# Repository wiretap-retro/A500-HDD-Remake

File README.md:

# A500 HDD Remake
A500 Side Expansion IDE

## Info
The A500 HDD Remake is an Amiga 500 ATA Expansion device that utilitizes ide.device to provide interface for a hard drive or CD-ROM. I use it in my A500 Tower, so I modified it with an activity light header and slightly different dimensions. 
\
\
Design attributed to John Tsiombika's A500hdd device, slightly modified. See additional details at: http://nuclear.mutantstargoat.com/hw

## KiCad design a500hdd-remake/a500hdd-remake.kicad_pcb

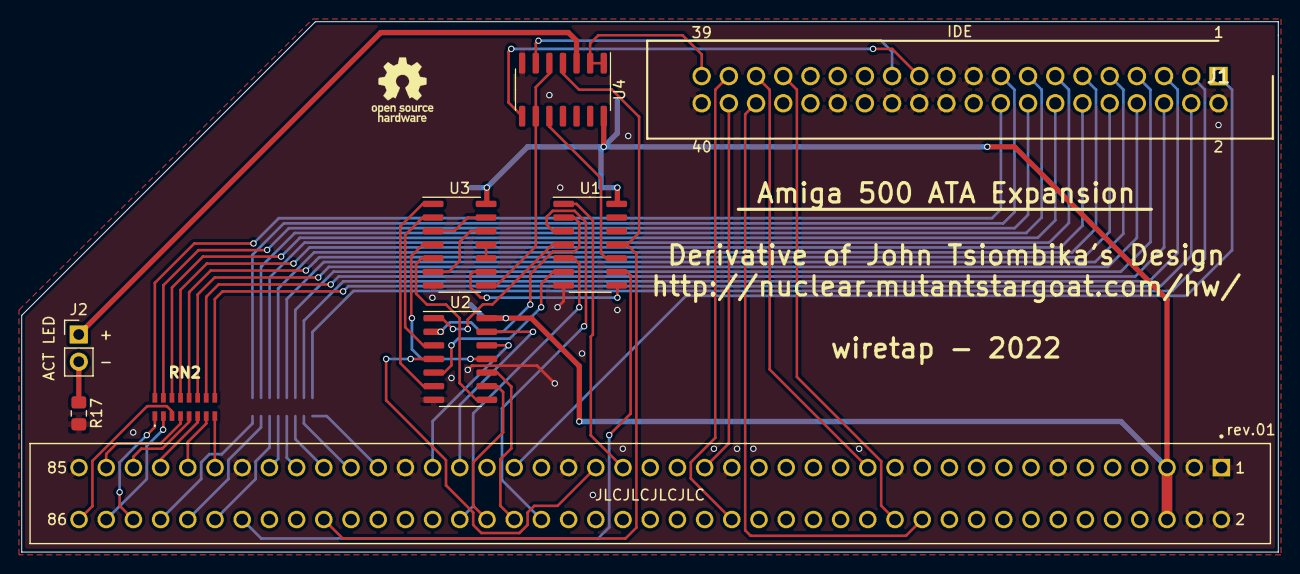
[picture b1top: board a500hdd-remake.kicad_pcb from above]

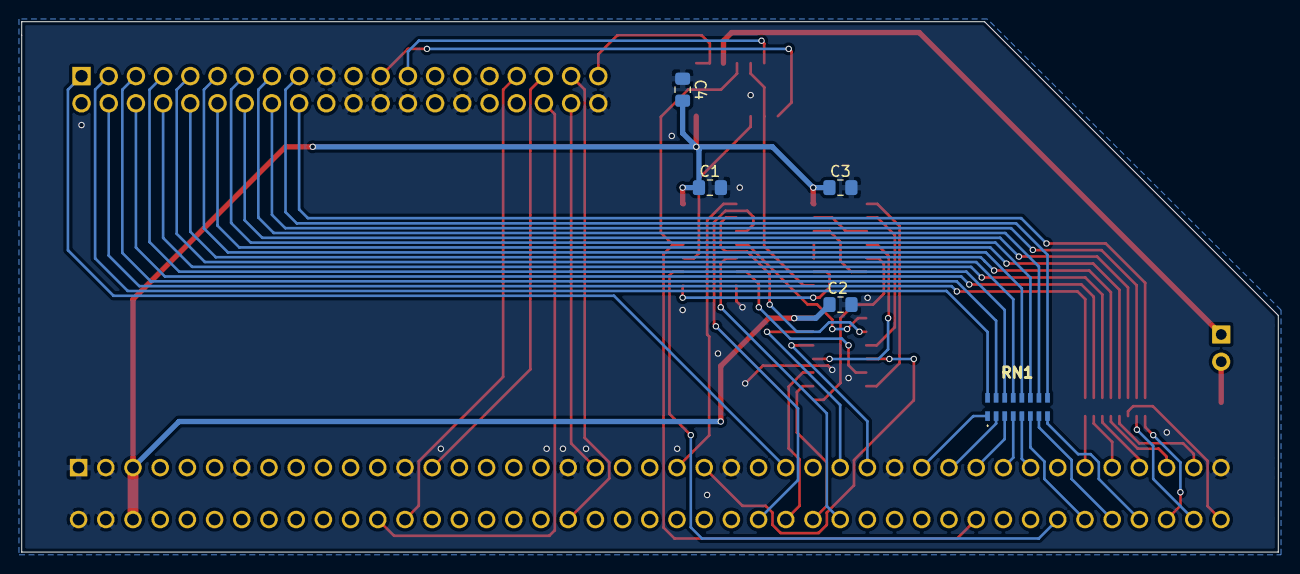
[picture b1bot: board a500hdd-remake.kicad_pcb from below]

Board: 2 copper layers, 117.3 x 49.5 mm, 14 parts (5 on the bottom side), 68 nets.

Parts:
BUS1: A500_SLOT; TE_1-5530843-0
C1, C2, C3, C4: C_Small; C_0805_2012Metric_Pad1.15x1.40mm_HandSolder
J1: 5103308-8; SHDR40W66P254_2X20_5829X914X986P
J2: Conn_01x02; PinHeader_1x02_P2.54mm_Vertical
R17: 330; R_0805_2012Metric_Pad1.15x1.40mm_HandSolder
RN1, RN2: 742C163680JP
U1: 74HCT04; SOIC-14_3.9x8.7mm_P1.27mm
U2, U3: 74LS08; SOIC-14_3.9x8.7mm_P1.27mm
U4: 74HCT00; SOIC-14_3.9x8.7mm_P1.27mm

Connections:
+5V: BUS1.5, BUS1.6, C1.2, C2.2, C3.2, C4.2, U1.14, U2.14, U3.14, U4.14
/A2: BUS1.27, J1.35
/A3: BUS1.26, J1.33
/A4: BUS1.24, J1.36
/A12: BUS1.38, J1.37
/A13: BUS1.39, J1.38
/D0: BUS1.75, RN2.8
/D1: BUS1.77, RN2.7
/D2: BUS1.79, RN2.6
/D3: BUS1.81, RN2.5
/D4: BUS1.83, RN2.4
/D5: BUS1.86, RN2.3
/D6: BUS1.84, RN2.2
/D7: BUS1.82, RN2.1
/D8: BUS1.80, RN1.8
/D9: BUS1.78, RN1.7
/D10: BUS1.76, RN1.6
/D11: BUS1.71, RN1.5
/D12: BUS1.69, RN1.4
/D13: BUS1.67, RN1.3
/D14: BUS1.65, RN1.2
/D15: BUS1.63, RN1.1
/IDE0: J1.17, RN1.9
/IDE1: J1.15, RN1.10
/IDE2: J1.13, RN1.11
/IDE3: J1.11, RN1.12
/IDE4: J1.9, RN1.13
/IDE5: J1.7, RN1.14
/IDE6: J1.5, RN1.15
/IDE7: J1.3, RN1.16
/IDE8: J1.4, RN2.9
/IDE9: J1.6, RN2.10
/IDE10: J1.8, RN2.11
/IDE11: J1.10, RN2.12
/IDE12: J1.12, RN2.13
/IDE13: J1.14, RN2.14
/IDE14: J1.16, RN2.15
/IDE15: J1.18, RN2.16
GND: BUS1.1, BUS1.2, BUS1.3, BUS1.4, BUS1.13, BUS1.25, BUS1.37, BUS1.49, BUS1.61, BUS1.73, BUS1.85, C1.1, C2.1, C3.1, C4.1, J1.2, J1.19, J1.22, J1.24, J1.26, J1.30, J1.40, R17.2, U1.7, U2.7, U3.7, U4.7
unnamed: BUS1.45, U1.1
unnamed: BUS1.47, U2.4
unnamed: BUS1.52, U1.3
unnamed: BUS1.53, J1.1
unnamed: BUS1.54, U2.10
unnamed: BUS1.56, U2.9
unnamed: BUS1.57, U2.13
unnamed: BUS1.58, U1.5
unnamed: BUS1.59, U2.12
unnamed: BUS1.68, U1.11, U4.4
unnamed: BUS1.74, U1.9
unnamed: J1.23, U4.8
unnamed: J1.25, U4.6
unnamed: J1.39, U4.1, U4.2
unnamed: J2.1, U4.3
unnamed: J2.2, R17.1
unnamed: U1.2, U2.2
unnamed: U1.4, U2.1
unnamed: U1.6, U2.5
unnamed: U1.8, U3.9
unnamed: U1.10, U4.10
unnamed: U2.3, U3.2
unnamed: U2.6, U3.1
unnamed: U2.8, U3.5
unnamed: U2.11, U3.4
unnamed: U3.8, U4.5, U4.9
unnamed: U3.10, U3.11
unnamed: U3.6, U3.12
unnamed: U3.3, U3.13

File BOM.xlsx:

Designator | Footprint | Comment
BUS1 | SamacSys_Parts:TE_1-5530843-0 | A500 Female Side Expansion Connector
C1,C2,C3,C4 | Capacitor_SMD:C_0805_2012Metric_Pad1.15x1.40mm_HandSolder | 0.1uF 0805 Capacitor
J1 | SHDR40W66P254_2X20_5829X914X986P | 5103308-8
J2 | Connector_PinHeader_2.54mm:PinHeader_1x02_P2.54mm_Vertical | 1x02 2.54mm Pin Header
R17 | Resistor_SMD:R_0805_2012Metric_Pad1.15x1.40mm_HandSolder | 330-ohm 0805 Resistor
RN1,RN2 | 742C163680JP | 742C163680JP
U1 | Package_SO:SOIC-14_3.9x8.7mm_P1.27mm | 74HCT04
U2,U3 | Package_SO:SOIC-14_3.9x8.7mm_P1.27mm | 74LS08
U4 | Package_SO:SOIC-14_3.9x8.7mm_P1.27mm | 74HCT00
